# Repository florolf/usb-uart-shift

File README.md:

# usb-uart-shift

This is an FT230X-based USB-UART adapter with built-in level shifting. This
allows talking to targets using different I/O voltage levels (1.8V to 5V), but
it's especially useful to avoid backpowering a target through the TX line.

This board can be assembled by JLCPCB PCBA for about $5 each, see the `fab/`
directory for Gerber/BOM/CPL data.

## Usage

The I/Os on the right-angle header (J1) are:

 * `->` (output, UART TX from the perspective of the adapter)
 * `<-` (input, RX)
 * `G` (GND)
 * `RTS` (output)
 * `CTS` (input)

The pins are arranged such that a 4-pin receptacle on the target is sufficient
when designing specifically for interfacing with this adapter if flow control
is not needed.

Level-shifting is configured through the 4-pin header (J2). When the I/O
reference voltage is available from the target it is recommended to connect it
to `Vt` and leave J2 open.

Alternatively, you can connect a jumper between `3.3` and `Vt` or `5` and `Vt`
on J2 to set the I/O voltage to 3.3V or 5V (strictly speaking USB VBUS),
respectively. However, in this case we cannot detect an unpowered target and
the usual backpowering considerations will apply. You can also just connect a
lab power supply to `Vt` and `G`.

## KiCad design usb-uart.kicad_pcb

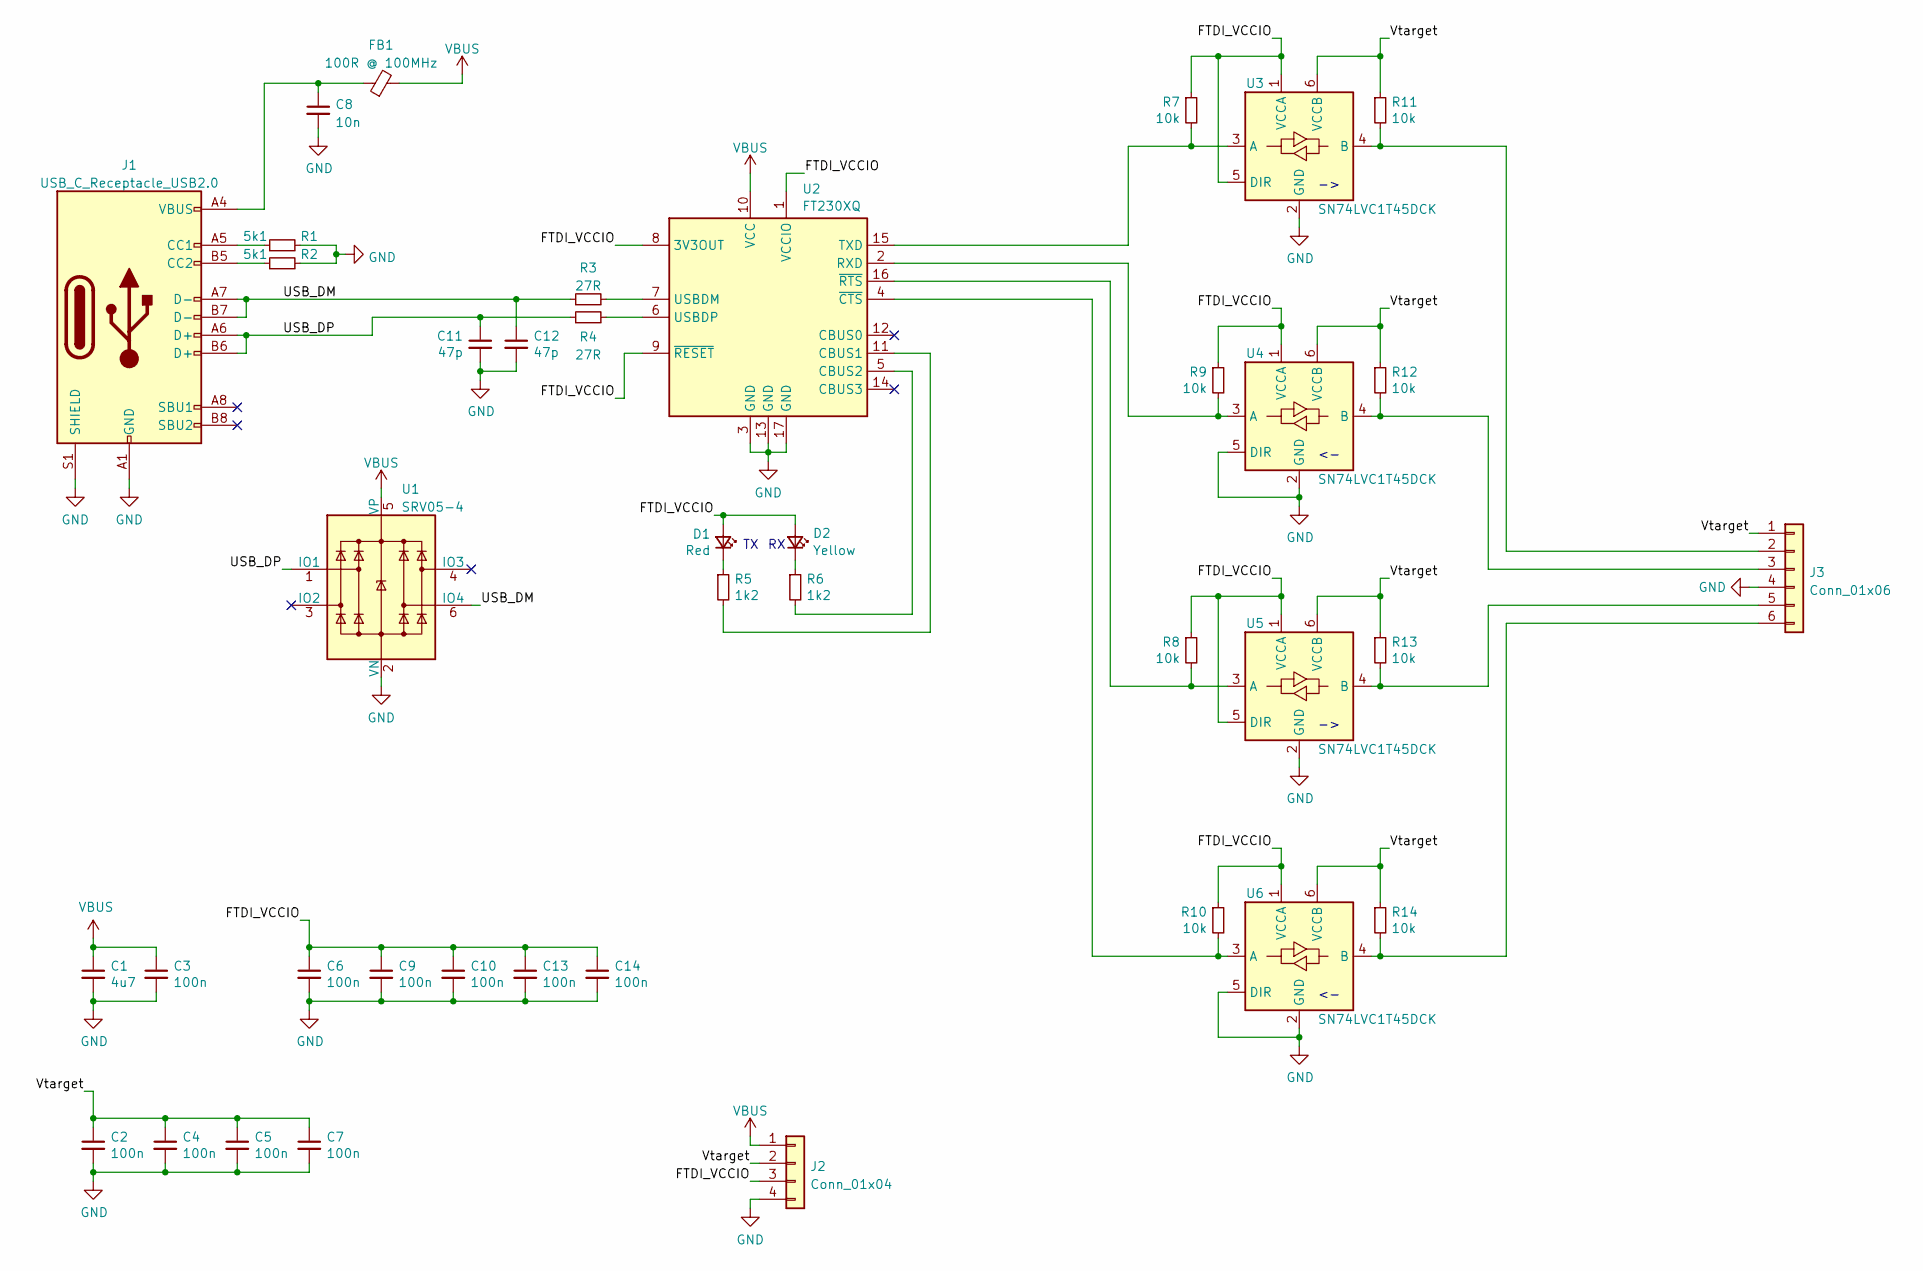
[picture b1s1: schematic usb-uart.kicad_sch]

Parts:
C1: 4u7; C_0603_1608Metric; MPN CL10A475KO8NNNC; JLCPCB C19666
C2, C3, C4, C5, C6, C7, C9, C10, C13, C14: 100n; C_0402_1005Metric; MPN CL05B104KB54PNC; JLCPCB C307331
C8: 10n; C_0402_1005Metric; JLCPCB C15195
C11, C12: 47p; C_0402_1005Metric; MPN 0402CG470J500NT; JLCPCB C1567
D1: Red; LED_0603_1608Metric; JLCPCB C2286
D2: Yellow; LED_0603_1608Metric; JLCPCB C72038
FB1: 100R @ 100MHz; L_0805_2012Metric; MPN GZ2012D101TF; JLCPCB C1015
J1: USB_C_Receptacle_USB2.0; USB_C_Receptacle_HRO_TYPE-C-31-M-12; MPN TYPE-C-31-M-12; JLCPCB C165948
J2: Conn_01x04; PinHeader_1x04_P2.54mm_Vertical; JLCPCB C6332197
J3: Conn_01x06; PinHeader_1x06_P2.54mm_Horizontal; JLCPCB C492414
R1, R2: 5k1; R_0402_1005Metric; MPN 0402WGF5101TCE; JLCPCB C25905
R3, R4: 27R; R_0603_1608Metric; JLCPCB C25190
R5, R6: 1k2; R_0402_1005Metric; JLCPCB C25862
R7, R8, R9, R10, R11, R12, R13, R14: 10k; R_0402_1005Metric; JLCPCB C25744
U1: SRV05-4; SOT-23-6; JLCPCB C85364
U2: FT230XQ; QFN-16-1EP_4x4mm_P0.65mm_EP2.1x2.1mm; MPN FT230XQ-R; JLCPCB C128629
U3, U4, U5, U6: SN74LVC1T45DCK; SOT-363_SC-70-6; MPN SN74LVC1T45DCKR; JLCPCB C9382

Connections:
/FTDI_VCCIO: C6.1, C9.1, C10.1, C13.1, C14.1, D1.2 (A), D2.2 (A), J2.3, R7.1, R8.1, R9.1, R10.1, U2.1 (VCCIO), U2.8 (3V3OUT), U2.9 (~RESET), U3.1 (VCCA), U3.5 (DIR), U4.1 (VCCA), U5.1 (VCCA), U5.5 (DIR), U6.1 (VCCA)
/USB_DM: C12.1, J1.A7 (D-), J1.B7 (D-), R3.1, U1.6 (IO4)
/USB_DP: C11.1, J1.A6 (D+), J1.B6 (D+), R4.1, U1.1 (IO1)
/Vtarget: C2.1, C4.1, C5.1, C7.1, J2.2, J3.1, R11.1, R12.1, R13.1, R14.1, U3.6 (VCCB), U4.6 (VCCB), U5.6 (VCCB), U6.6 (VCCB)
GND: C1.2, C2.2, C3.2, C4.2, C5.2, C6.2, C7.2, C8.2, C9.2, C10.2, C11.2, C12.2, C13.2, C14.2, J1.A1 (GND), J1.A12 (GND), J1.B1 (GND), J1.B12 (GND), J1.S1 (SHIELD), J2.4, J3.4, R1.2, R2.2, U1.2 (VN), U2.3 (GND), U2.13 (GND), U2.17 (GND), U3.2 (GND), U4.2 (GND), U4.5 (DIR), U5.2 (GND), U6.2 (GND), U6.5 (DIR)
unnamed: C8.1, FB1.1, J1.A4 (VBUS), J1.A9 (VBUS), J1.B4 (VBUS), J1.B9 (VBUS)
unnamed: D1.1 (K), R5.1
unnamed: D2.1 (K), R6.1
unnamed: J1.A5 (CC1), R1.1
unnamed: J1.B5 (CC2), R2.1
unnamed: J3.2, R11.2, U3.4 (B)
unnamed: J3.3, R12.2, U4.4 (B)
unnamed: J3.5, R13.2, U5.4 (B)
unnamed: J3.6, R14.2, U6.4 (B)
unnamed: R5.2, U2.11 (CBUS1)
unnamed: R6.2, U2.5 (CBUS2)
unnamed: R9.2, U2.2 (RXD), U4.3 (A)
unnamed: R7.2, U2.15 (TXD), U3.3 (A)
unnamed: R3.2, U2.7 (USBDM)
unnamed: R4.2, U2.6 (USBDP)
unnamed: R10.2, U2.4 (~CTS), U6.3 (A)
unnamed: R8.2, U2.16 (~RTS), U5.3 (A)
VBUS: C1.1, C3.1, FB1.2, J2.1, U1.5 (VP), U2.10 (VCC)

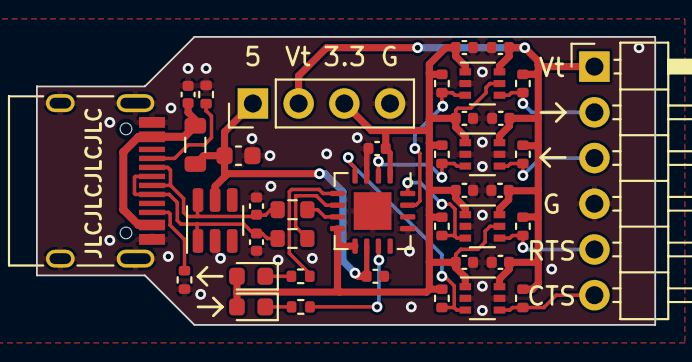
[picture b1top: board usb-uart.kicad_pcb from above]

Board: 2 copper layers, 34.3 x 16.0 mm, 40 parts (0 on the bottom side), 23 nets.

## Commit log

2025-05-14 import
2025-05-17 add fab files
    Include the fab files in the repo for convenience so people can just
    order the boards directly.
